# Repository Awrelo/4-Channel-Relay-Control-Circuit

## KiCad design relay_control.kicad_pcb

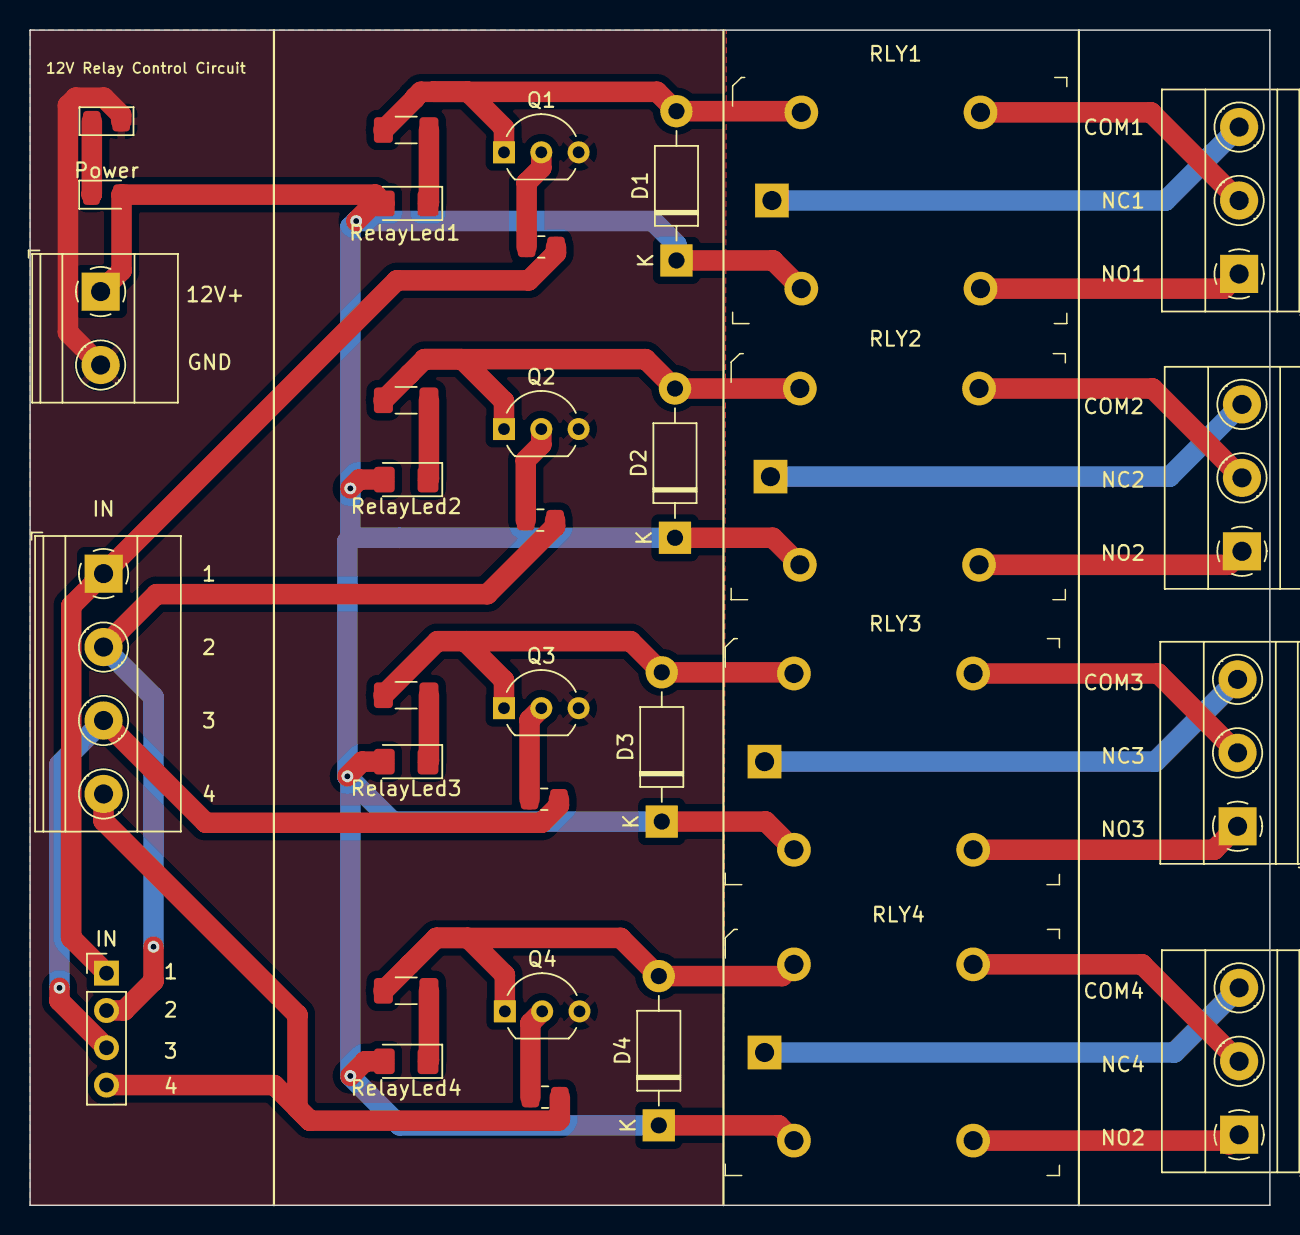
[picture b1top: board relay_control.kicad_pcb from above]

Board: 2 copper layers, 84.4 x 80.0 mm, 33 parts (0 on the bottom side), 31 nets.

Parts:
12V+: Screw_Terminal_01x02; TerminalBlock_Phoenix_MKDS-1,5-2_1x02_P5.00mm_Horizontal
D1, D2, D3, D4: 1N4007; D_DO-41_SOD81_P10.16mm_Horizontal
IN: Screw_Terminal_01x04; TerminalBlock_Phoenix_MKDS-1,5-4_1x04_P5.00mm_Horizontal
IN#2: Screw_Terminal_01x04; PinHeader_1x04_P2.54mm_Vertical
J1, J2, J4: Screw_Terminal_01x03; TerminalBlock_Phoenix_MKDS-1,5-3_1x03_P5.00mm_Horizontal
NO1: Screw_Terminal_01x03; TerminalBlock_Phoenix_MKDS-1,5-3_1x03_P5.00mm_Horizontal
Power: LED; LED_0805_2012Metric_Pad1.15x1.40mm_HandSolder
Q1, Q2, Q3, Q4: BC548; TO-92_Inline_Wide
R1, R2, R3, R4: 1K; R_0805_2012Metric_Pad1.20x1.40mm_HandSolder
RLY5, RLY6, RLY7, RLY8: G5LE-14_DC12; Relay_THT_G5LE-14
RelayLed1, RelayLed2, RelayLed3, RelayLed4: LED; LED_1206_3216Metric_Pad1.42x1.75mm_HandSolder
Rly1, Rly2, Rly3, Rly4: R; R_1206_3216Metric_Pad1.30x1.75mm_HandSolder
Rp1: R; R_0805_2012Metric_Pad1.20x1.40mm_HandSolder

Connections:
12V: 12V+.1, D1.1 (K), D2.1 (K), D3.1 (K), D4.1 (K), Power.2 (A), RLY5.2 (COIL), RLY6.2 (COIL), RLY7.2 (COIL), RLY8.2 (COIL), RelayLed1.2 (A), RelayLed2.2 (A), RelayLed3.2 (A), RelayLed4.2 (A)
GND: 12V+.2, Q1.3 (E), Q2.3 (E), Q3.3 (E), Q4.3 (E), Rp1.2
unnamed: D1.2 (A), Q1.1 (C), RLY6.5 (COIL), Rly1.2
unnamed: D3.2 (A), Q3.1 (C), RLY5.5 (COIL), Rly3.2
unnamed: D4.2 (A), Q4.1 (C), RLY7.5 (COIL), Rly4.2
unnamed: D2.2 (A), Q2.1 (C), RLY8.5 (COIL), Rly2.2
unnamed: J1.1, RLY6.3 (NO)
unnamed: J1.2, RLY6.4 (NC)
unnamed: J1.3, RLY6.1 (COM)
unnamed: J2.1, RLY8.3 (NO)
unnamed: J2.2, RLY8.4 (NC)
unnamed: J2.3, RLY8.1 (COM)
unnamed: NO1.1, RLY5.3 (NO)
unnamed: NO1.2, RLY5.4 (NC)
unnamed: NO1.3, RLY5.1 (COM)
unnamed: J4.1, RLY7.3 (NO)
unnamed: J4.2, RLY7.4 (NC)
unnamed: J4.3, RLY7.1 (COM)
unnamed: Power.1 (K), Rp1.1
unnamed: Q1.2 (B), R1.2
unnamed: Q2.2 (B), R4.2
unnamed: Q3.2 (B), R2.2
unnamed: Q4.2 (B), R3.2
unnamed: RelayLed1.1 (K), Rly1.1
unnamed: RelayLed2.1 (K), Rly2.1
unnamed: RelayLed3.1 (K), Rly3.1
unnamed: RelayLed4.1 (K), Rly4.1
RLY1: IN.1, IN#2.1, R1.1
RLY2: IN.2, IN#2.2, R4.1
RLY3: IN.3, IN#2.3, R2.1
RLY4: IN.4, IN#2.4, R3.1
